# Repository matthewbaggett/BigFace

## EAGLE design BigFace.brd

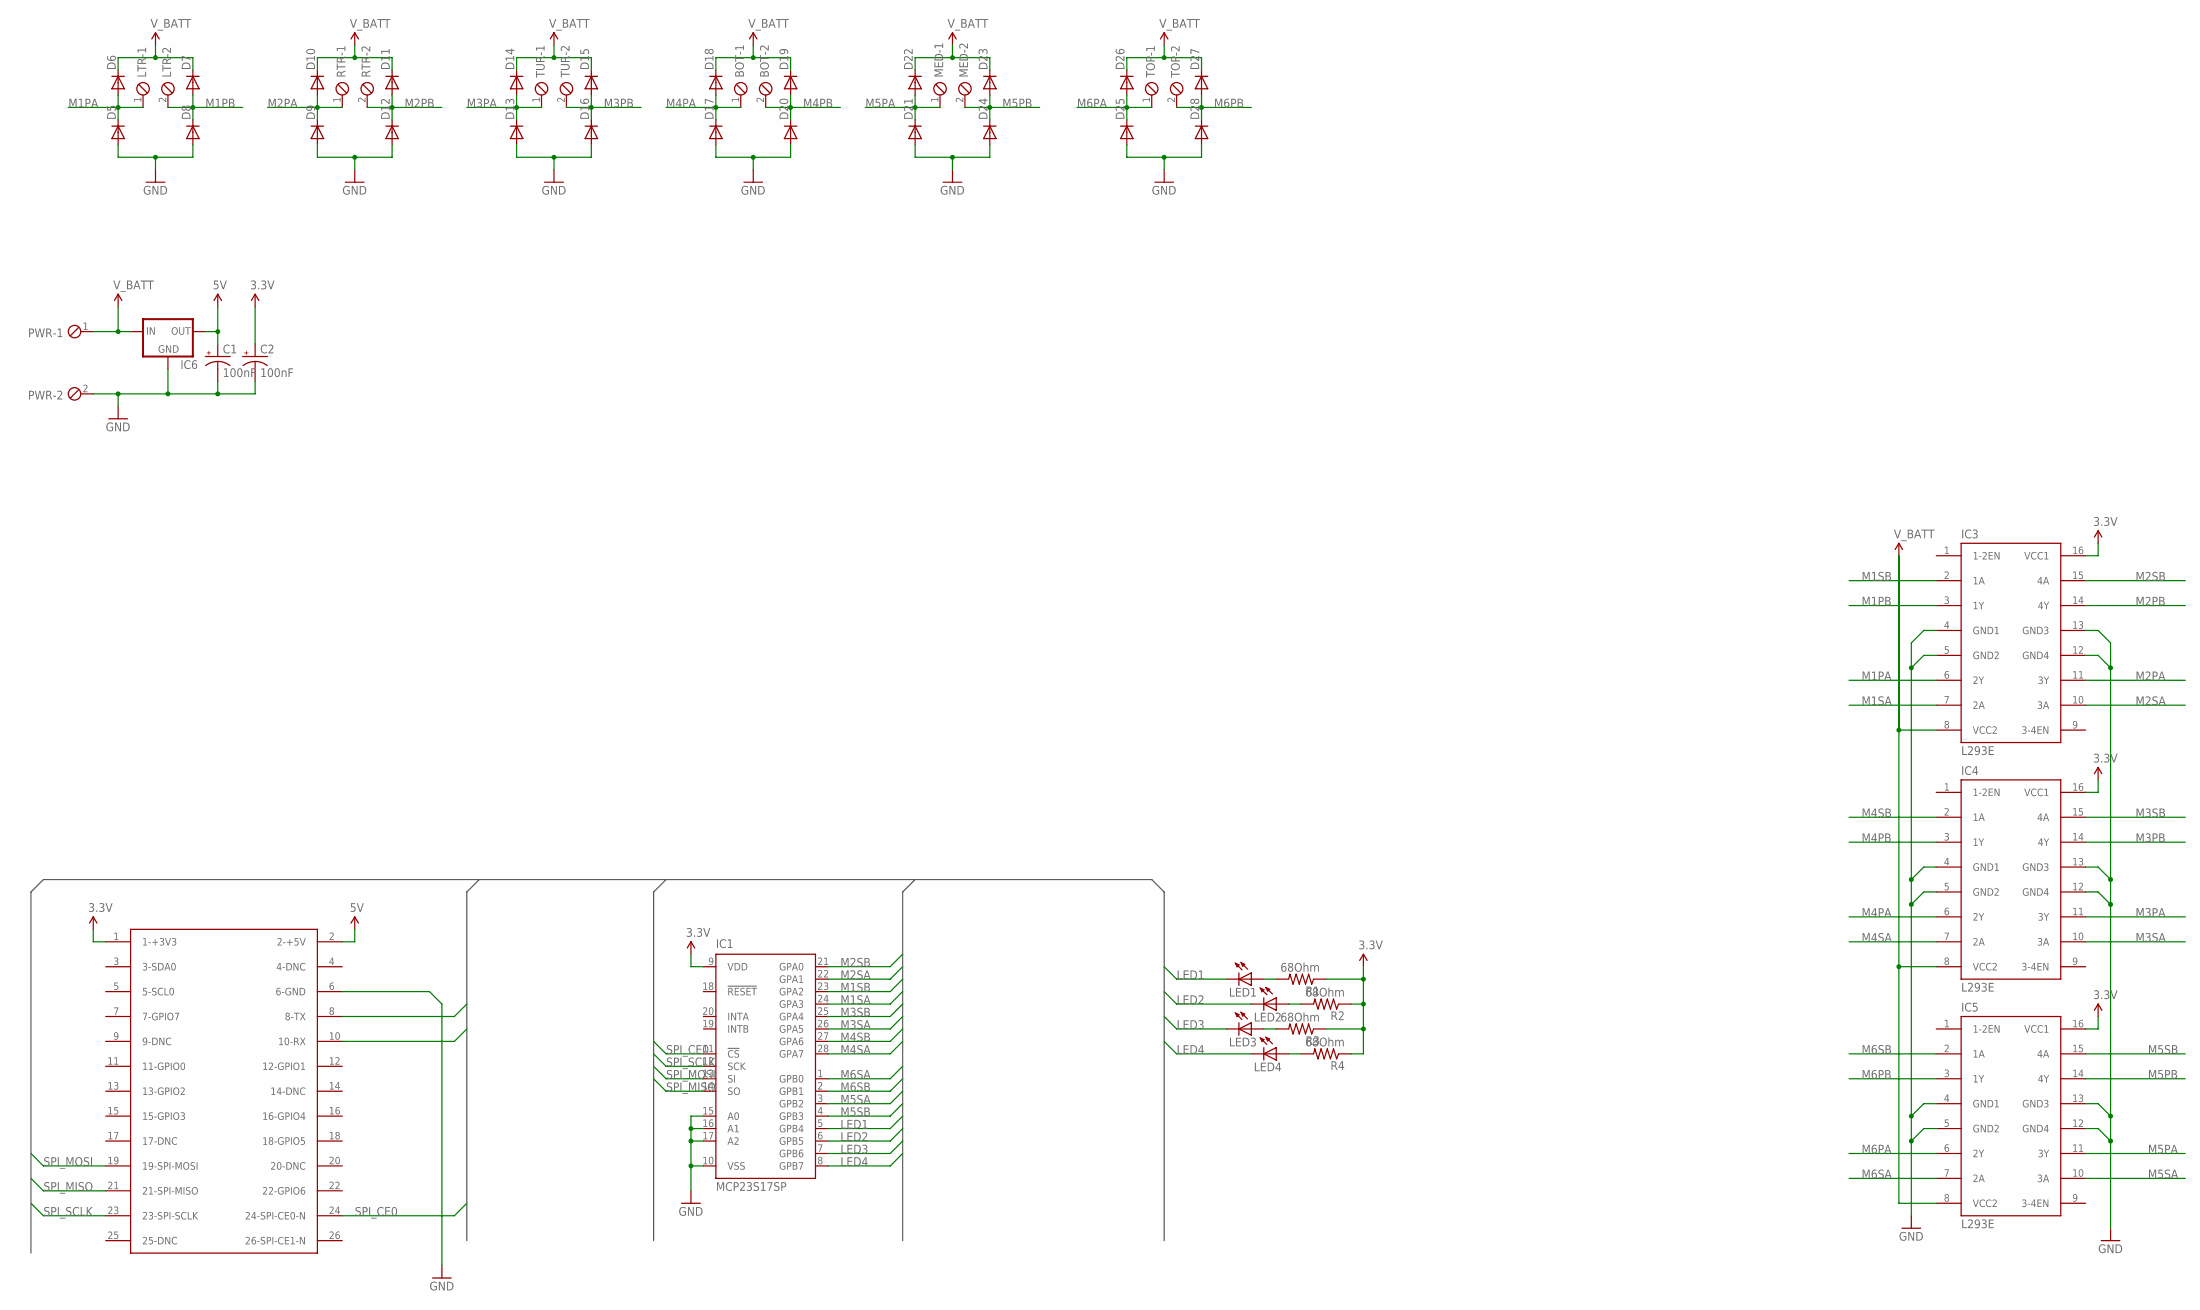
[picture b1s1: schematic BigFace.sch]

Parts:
BOT: MPT2; 2POL254
C1, C2: 100nF; CPOL-RADIAL-10UF-25V
D5, D6, D7, D8, D9, D10, D11, D12, D13, D14, D15, D16, D17, D18, D19, D20, D21, D22, D23, D24, D25, D26, D27, D28: DIODE1N4148; DIODE-1N4148
IC1: MCP23S17SP; DIL28-3
IC3, IC4, IC5: L293E; DIL16
IC6: V_REG_78XXSINK; TO220-IGO
LED1, LED2, LED3, LED4: LED3MM
LTR: MPT2; 2POL254
MED: MPT2; 2POL254
PWR: MPT2; 2POL254
R1, R2, R3, R4: 68Ohm; AXIAL-0.3EZ
RTR: MPT2; 2POL254
TOP: MPT2; 2POL254
TUR: MPT2; 2POL254
U$1: RASPBERRY-PI

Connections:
3.3V: C2.1 (+), IC1.9 (VDD), IC3.16 (VCC1), IC4.16 (VCC1), IC5.16 (VCC1), R1.P$1 (1), R2.P$1 (1), R3.P$1 (1), R4.P$1 (1), U$1.1 (1-+3V3)
5V: C1.1 (+), IC6.OUT, U$1.2 (2-+5V)
GND: C1.2 (-), C2.2 (-), D5.A, D8.A, D9.A, D12.A, D13.A, D16.A, D17.A, D20.A, D21.A, D24.A, D25.A, D28.A, IC1.10 (VSS), IC1.15 (A0), IC1.16 (A1), IC1.17 (A2), IC3.4 (GND1), IC3.5 (GND2), IC3.12 (GND4), IC3.13 (GND3), IC4.4 (GND1), IC4.5 (GND2), IC4.12 (GND4), IC4.13 (GND3), IC5.4 (GND1), IC5.5 (GND2), IC5.12 (GND4), IC5.13 (GND3), IC6.GND, PWR.2, U$1.6 (6-GND)
LED1: IC1.5 (GPB4), LED1.K (C)
LED2: IC1.6 (GPB5), LED2.K (C)
LED3: IC1.7 (GPB6), LED3.K (C)
LED4: IC1.8 (GPB7), LED4.K (C)
M1PA: D5.C, D6.A, IC3.6 (2Y), LTR.1
M1PB: D7.A, D8.C, IC3.3 (1Y), LTR.2
M1SA: IC1.24 (GPA3), IC3.7 (2A)
M1SB: IC1.23 (GPA2), IC3.2 (1A)
M2PA: D9.C, D10.A, IC3.11 (3Y), RTR.1
M2PB: D11.A, D12.C, IC3.14 (4Y), RTR.2
M2SA: IC1.22 (GPA1), IC3.10 (3A)
M2SB: IC1.21 (GPA0), IC3.15 (4A)
M3PA: D13.C, D14.A, IC4.11 (3Y), TUR.1
M3PB: D15.A, D16.C, IC4.14 (4Y), TUR.2
M3SA: IC1.26 (GPA5), IC4.10 (3A)
M3SB: IC1.25 (GPA4), IC4.15 (4A)
M4PA: BOT.1, D17.C, D18.A, IC4.6 (2Y)
M4PB: BOT.2, D19.A, D20.C, IC4.3 (1Y)
M4SA: IC1.28 (GPA7), IC4.7 (2A)
M4SB: IC1.27 (GPA6), IC4.2 (1A)
M5PA: D21.C, D22.A, IC5.11 (3Y), MED.1
M5PB: D23.A, D24.C, IC5.14 (4Y), MED.2
M5SA: IC1.3 (GPB2), IC5.10 (3A)
M5SB: IC1.4 (GPB3), IC5.15 (4A)
M6PA: D25.C, D26.A, IC5.6 (2Y), TOP.1
M6PB: D27.A, D28.C, IC5.3 (1Y), TOP.2
M6SA: IC1.1 (GPB0), IC5.7 (2A)
M6SB: IC1.2 (GPB1), IC5.2 (1A)
unnamed: LED4.A, R4.P$2 (2)
unnamed: LED3.A, R3.P$2 (2)
unnamed: LED2.A, R2.P$2 (2)
unnamed: LED1.A, R1.P$2 (2)
SPI_CE0: IC1.11 (!CS), U$1.24 (24-SPI-CE0-N)
SPI_MISO: IC1.14 (SO), U$1.21 (21-SPI-MISO)
SPI_MOSI: IC1.13 (SI), U$1.19 (19-SPI-MOSI)
SPI_SCLK: IC1.12 (SCK), U$1.23 (23-SPI-SCLK)
V_BATT: D6.C, D7.C, D10.C, D11.C, D14.C, D15.C, D18.C, D19.C, D22.C, D23.C, D26.C, D27.C, IC3.8 (VCC2), IC4.8 (VCC2), IC5.8 (VCC2), IC6.IN, PWR.1

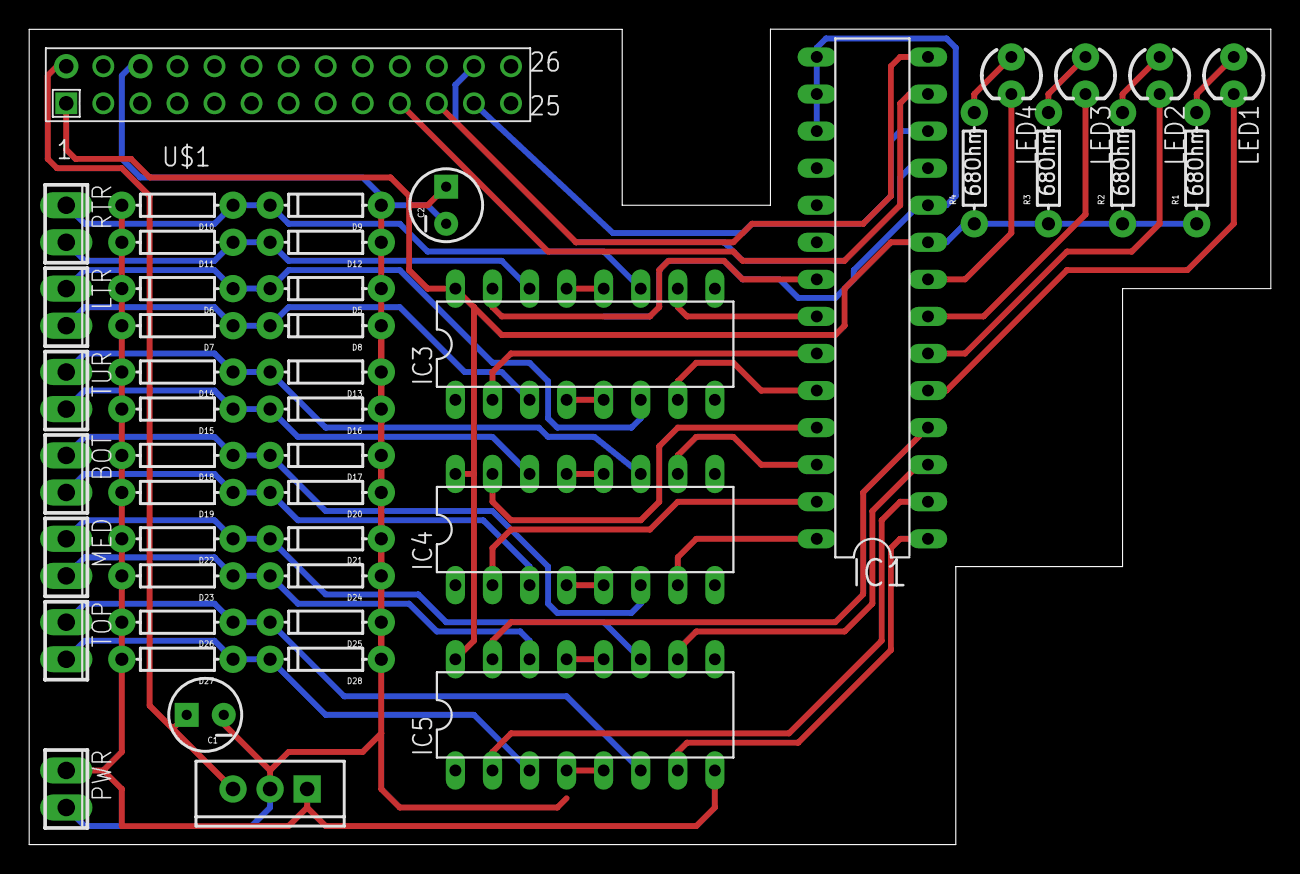
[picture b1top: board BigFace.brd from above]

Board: 2 copper layers, 85.1 x 55.9 mm, 47 parts (0 on the bottom side), 40 nets.

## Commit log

2013-10-25 Initial version of BigFace. I wonder if this board even works.
2013-10-25 adding the raspberry pi footprint part.
2013-10-25 Panelised?
2013-10-25 Adding screencaps
2013-10-25 Adding gitignore
2013-10-25 Deleting eagle cache files
2013-10-25 Do not store cache files
2013-10-25 Updated project
2013-10-25 Updated BRD/SCH
2013-10-25 Adding sparkfuns gerber-making magic
2013-10-25 Adding Gerber files.

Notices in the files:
parts and their libraries:
SparkFun-DiscreteSemi: Licensing: CC v3.0 Share-Alike You are welcome to use this library for commercial purposes.
